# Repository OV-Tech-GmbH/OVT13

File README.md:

# OVT13
Open-source thin-and-light 13" laptop
## Table of contents

1. Electronics
   - Keyboard PCB
   - Webcam PCB
   - Trackpad PCBs
2. Mechanical
   - Keyboard
3. Software
   - Keyboard firmware and source files

## Details of content

1. Electronics
   - Keyboard PCB: <br /> <br /> 
***General description:*** <br /> <br /> This module is a separate standalone and thinly-designed electromechanical keyboard for the open-source laptop. It provides a distinct hardware abstraction via USB2.0 connectivity to simplify integration into a laptop or computer system. An RP2040 microcontroller constantly evaluates the states of the keyswitches and controls the lightning. Regarding the power supply only a voltage of 5V DC is needed to completly supply the electronics, all other voltages for digital logic and LED-driving are being generated on the PCB. Once connected to an USB Host in a computer system, the microcontroller acts as an USB Device and registers itself as an USB HID keyboard device. With this configuration no custom drivers are needed which contributes to an os-independend (Windows, Linux, etc.) and timeless integration concept. The firmware of the microcontroller is based on the open-source keyboard framework QMK. Once an USB-connection is established, standard scancodes are being transmitted to the computer system which then will be mapped into keycodes. The hardware connectivity to the mainboard of the laptop is realized over an spring-header connector receptable which includes all electrical signals and the power supply. For the firmware to load onto the RP2040, only one pin of the spring header receptable must change its logical state. The RP2040 register itself as an USB-memory device which then can be accessed via the os` filesystem. It is possible to load the firmware file per drag&drop onto the microcontroller. <br /> <br /> 
***Electrical specification***<br /> <br /> 
__PCB front view__

The PCB-front consists of the keyswitches from the manufacturer Khail. The design integrates a complete set of keys without the numerical part. Keycaps can be assembled on top of the keyswitches.
Inside the keyswitches there is a transparent cabin to integrate LED components and other small components like the anti-ghosting diode. Per keyswitch a white LED and an RGB LED is placed to keep the option to build a keyboard with either white backlightning or RGB backlightning. 
<br /><br /> __PCB back view__ <br />
On the backside of the PCB there are all remaining components located. The remaing components include the microcontroller RP2040 and its peripheral circuitry, voltage generation, ESD-protection and other parts of the keyswitch matrix.
 <br />
<br /> __PCB layerstack and routing__ <br /> The Layerstack consists four layers of copper and it is taken from the 4-Layer JLCPCB stackup JLC04161H-7628. An impedance profile 90Ohms is included for the USB connection. The layerstack looks as follows: Top-layer: Signal, Mid1-layer: GND, Mid2-layer PWR/GND, Bottom-layer: Signal 
On the top layer all signals and power supplies regarding the LED-backlightning are routed:

The Mid1-layer includes a continuous ground plane to provide good electrical characteristics. The Mid2-layer is a mix of power plane distribution and ground islands, especially for the dense placement of the microcontroller and surrounding circuitry:

On the bottom layer consist of the routing of the keyswitch matrix, the microcontroller and the remaining circuitry.

   - Trackpad PCBs:<br /> <br /> 
***General description:***<br /> <br /> The design of the trackpad module consists of two printed circuit boards. The first one consists of the touch-sensitive matrix which, can be influenced by the user. In order to keep variations and negative impact factors away from the matrix, the touch sensing IC and its digital communication partner are located on an evaluation board. Both boards are connected via an flex-pcb cable section so the touch IC can to read the sensing matrix.<br /> <br /> 
<br /> <br />
__1. Trackpad sensor PCB electrical specification:__<br /> <br />
The top side of the PCB consists of touch-sensitive elements in the form of diamonds arranged in rows and columns. The gaps between the diamonds form capacitive elements that can be controlled and thus read by the touch IC. The capacitive elements generate an electric field, that is deflected when the user`s finger approaches. The change in the field and thus the resulting capacitance and charge can be measured and converted into a finger position sensor. <br /> <br />

<br /> <br />
On the backside of the pcb a flex pcb connector and a snap dome are located. The flex connector is used to connect the board to another board on which a touch IC is located via a flex cable. The snap dome is being used to generate the function of a button press. When pressed, the entire row and colum is shorted and the rapid change in capacitance and therefore charge is recognised and interpreted as a button press. <br /> <br />

<br /> <br />__2. Trackpad evaluation PCB electrical specification:__<br /> <br />
This PCB is designed as a flex PCB with two stiffened sections. The section where all the components are located is fitted with a FR4-stiffener. The section designed as a flex cable contains no stiffeners in order to utilise the flexibility of a flex cable. The last section is the connector tongue itself and the stiffener is made out of polyimide to fulfil the thickness insertion requierements of the ffc-connector on the trackpad PCB.
<br /> <br />
<br /> <br />
The evaluation board is used to collect trackpad touch data and turn it into an USB HID mouse. This level of integration abstracts the custom interface to a simple USB connection without the need for special drivers or hardware to utilise the touch data. The IQS9150 IC performs the sampling and processing of the trackpad touches and snapdome clicks and reports the data to an RP2040, which performs some further processing, such as interpreting a click event as a left or right mouse button click. The RP2040 streams the touch data in USB HID mouse format to an USB host and thus acts as an I2C USB bridge. Additional connections for programming and evaluating the two ICs and other devices such as test buttons are provided on the board for development purposes. The final board will contain only the two ICs, some necessary external circuitry and an USB connection. This makes integration into the laptop easy and follows the concept of a timeless and modular design.
<br /> <br />
<br /> <br />

3. Mechanical
   - Keyboard: -

4. Software
   - Keyboard PCB: The firmware of the keyboard was created using the framework QMK. The framework provides all basic keyboard functions such as matrix scanning, USB communication, lightning and much more. Therefore, only one module of the keyboard project has been created for the specific design of the keyboard. Minor modifications were made to the QMK core to compile the firmware for the RP2040 microcontroller. A standard English keyboard layout (QWERTY) was used. Details of the code project can be found in the subfolder for the keyboard software.

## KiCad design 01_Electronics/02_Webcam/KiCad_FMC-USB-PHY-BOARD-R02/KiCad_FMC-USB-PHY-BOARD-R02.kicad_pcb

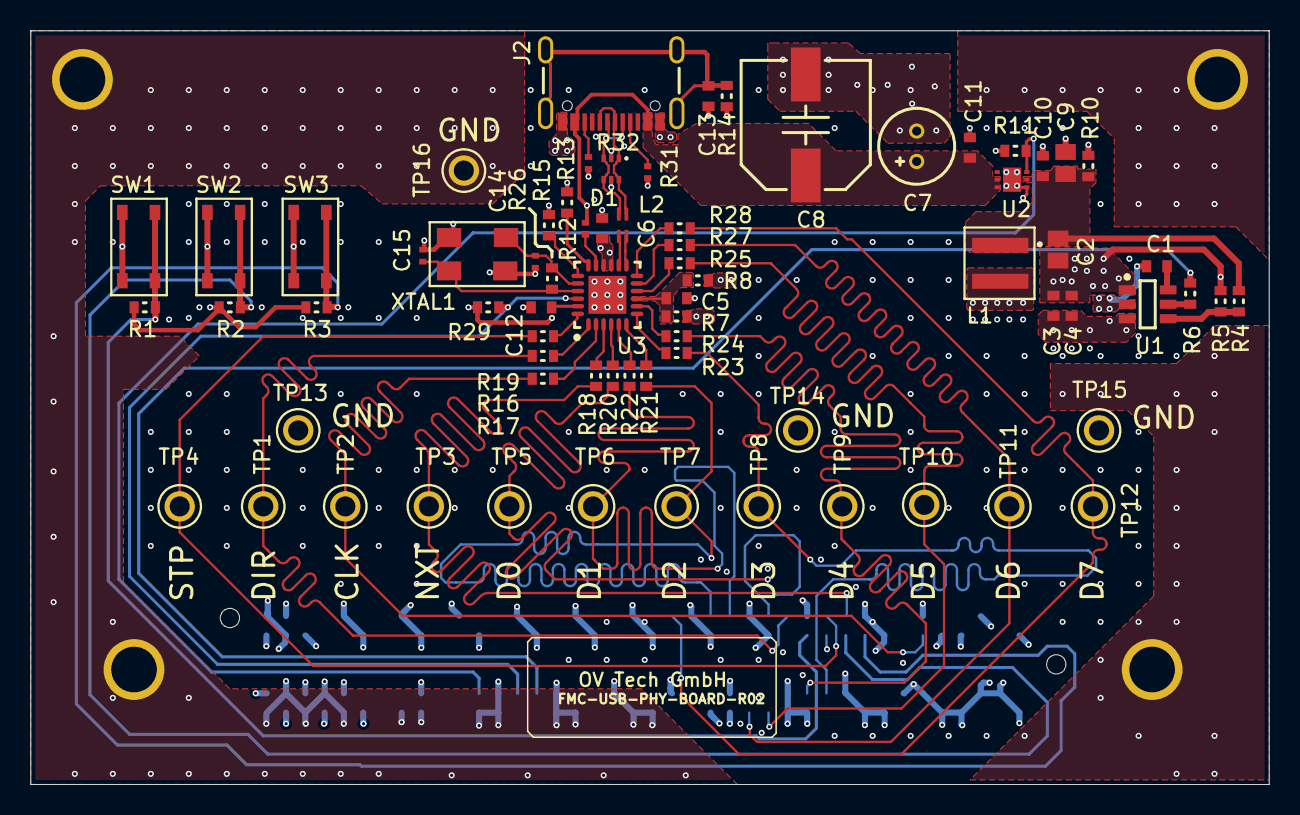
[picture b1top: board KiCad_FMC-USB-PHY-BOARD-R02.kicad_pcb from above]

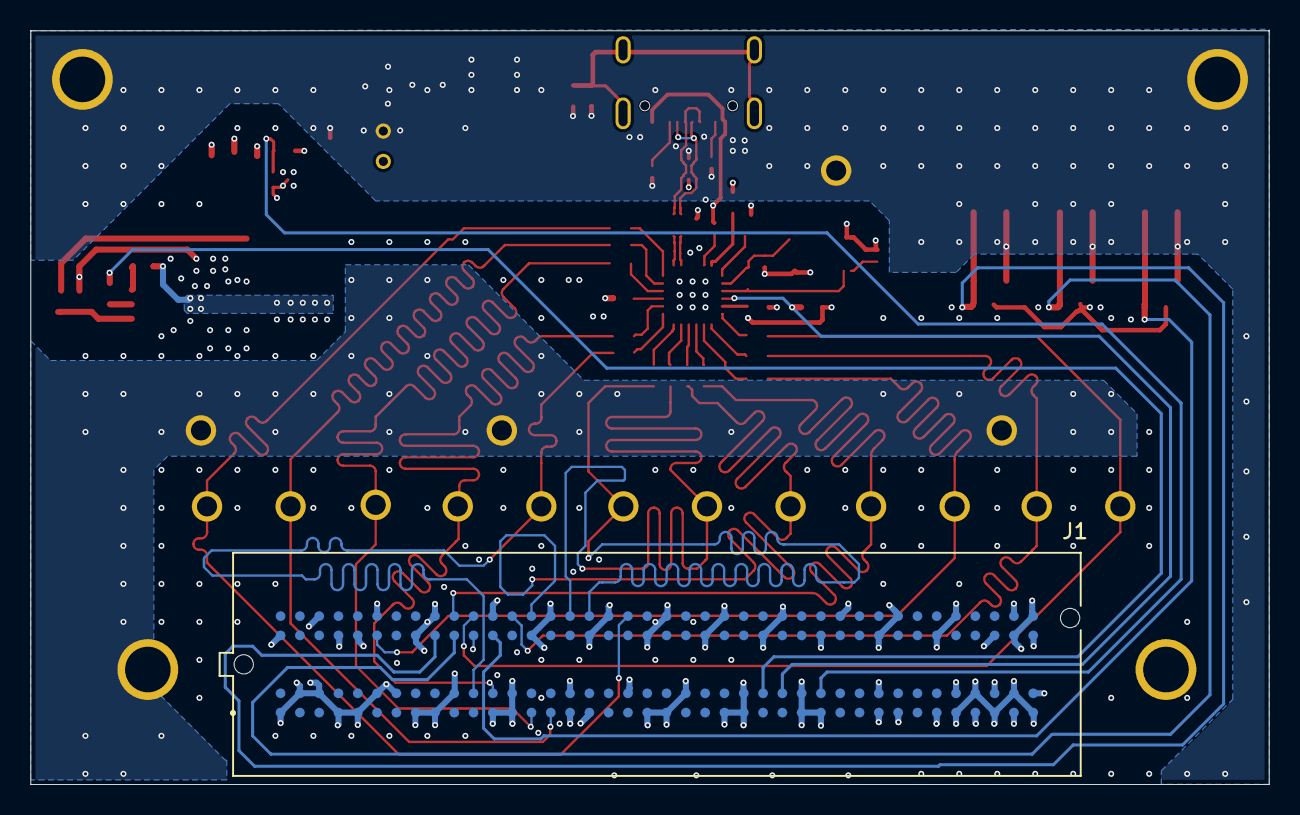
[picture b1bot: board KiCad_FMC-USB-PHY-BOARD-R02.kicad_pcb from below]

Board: 4 copper layers, 81.5 x 49.6 mm, 77 parts (3 on the bottom side), 54 nets.

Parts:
C1, C4, C5, C10, C11, C13: 100nF 100V; CAPC1608X10L
C2: 33µF 10V; CAPC2012X14L
C3: 2.2µF 35V; CAPC1608X10L
C6, C12: 1µF 16V; CAPC1608X10L
C7: 100µF 10V; CAP_Radial_5x8mm
C8: 22µF 63V; CAPAE9083X70N
C9: 10µF 16V; CAPC2012X14L
C14, C15: 30pF 50V; CAPC1005X06L
D1: 82400152; WE-TVS_SOT563
J1: ASP-134604-01; BOARD-TO-BOARD CON SAMTEC_ASP-134604-01
J2: TYPE-C 16PIN 2MD(073); USB Type C - TYPE-C 16PIN 2MD(073)
L1: 6.8µH 3.75A; WE-MAPI_4030
L2: 90Ohm 100mA; WE-CNSW_0603
MP1, MP2, MP3, MP4: MP_MOUNT_3MM_Plated; MP_3MM_PLATED
R1, R2, R3, R11, R29: 22kOhm 1%; RESC1608X04L
R4: 100kOhm 1%; RESC1608X04L
R5: 13.7kOhm 1%; RESC1608X04L
R6, R7, R8, R13, R16, R18, R19, R20, R21, R22, R23, R24, R25, R27, R28: 0 Ohm; RESC1608X04L
R10: 10kOhm 1%; RESC1608X04L
R12: 10k 1%; RESC1005X04L
R14: 330Ohm 1%; RESC1608X04L
R15: 8.06kOhm 1%; RESC1608X04L
R17: 33Ohm 1%; RESC1608X04L
R26: 1MOhm 1%; RESC1608X04L
R31, R32: 5.1k 1%; RESC1005X04L
SW1, SW2, SW3: PTS815 SJM 250 SMTR LFS; SW_TACT_PTS815 SJM 250 SMTR LFS
TP1, TP2, TP3, TP4, TP5, TP6, TP7, TP8, TP9, TP10, TP11, TP12, TP13, TP14, TP15, TP16: 4952; TP_KEYSTONE_4952
U1: TPS54308DDC; SOT95P280X110-6N
U2: AP21510FM-7; QFN50P201X181X60_HS-7N
U3: USB3343; QFN50P400X400X100_HS-25M
XTAL1: ECS-260-18-30B-AGM-TR; XTAL_ECX-53B_5X3.2X0.85

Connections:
1V8_ADJ: J1.G39, J1.H40, R1.2, R2.2, R3.2, R7.2, R29.2
3V3: C6.1, J1.C39, J1.D32, J1.D36, J1.D38, J1.D40, R8.2, R13.2, U3.15, U3.16
5V0: C2.1, C9.1, C10.1, L1.1, R4.1, R10.2, U2.2
12V0: C3.1, C4.1, J1.C35, J1.C37, U1.3
DEBUG_SW1: J1.G12, R1.1, SW1.3, SW1.4
DEBUG_SW2: J1.G10, R2.1, SW2.3, SW2.4
DEBUG_SW3: J1.G9, R3.1, SW3.3, SW3.4
GND: C2.2, C3.2, C4.2, C5.2, C6.2, C7.2, C8.2, C9.2, C10.2, C11.2, C12.2, C13.2, C14.2, C15.2, D1.2, J1.C1, J1.C4, J1.C5, J1.C8, J1.C9, J1.C12, J1.C13, J1.C16, J1.C17, J1.C20, J1.C21, J1.C24, J1.C25, J1.C28, J1.C29, J1.C32, J1.C33, J1.C36, J1.C38, J1.C40, J1.D2, J1.D3, J1.D6, J1.D7, J1.D10, J1.D13, J1.D16, J1.D19, J1.D22, J1.D25, J1.D28, J1.D37, J1.D39, J1.G1, J1.G4, J1.G5, J1.G8, J1.G11, J1.G14, J1.G17, J1.G20, J1.G23, J1.G26, J1.G29, J1.G32, J1.G35, J1.G38, J1.G40, J1.H3, J1.H6, J1.H9, J1.H12, J1.H15, J1.H18, J1.H21, J1.H24, J1.H27, J1.H30, J1.H33, J1.H36, J1.H39, J2.A1/B12, J2.A12/B1, MP1.1, MP2.1, MP3.1, MP4.1, R5.1, R10.1, R11.1, R14.1, R15.2, R31.1, R32.1, SW1.1, SW1.2, SW2.1, SW2.2, SW3.1, SW3.2, TP13.TP, TP14.TP, TP15.TP, TP16.TP, U1.1, U2.1, U2.7, U3.25, XTAL1.2, XTAL1.4
NetC1_1: C1.1, U1.6
NetC1_2: C1.2, L1.2, U1.2
NetC5_1: C5.1, R7.1, R8.1, U3.9
NetC12_1: C12.1, U3.23
NetC13_1: C13.1, J2.SHD, R14.2
NetJ2_A5: J2.A5, R31.2
NetJ2_B5: J2.B5, R32.2
NetR4_2: R4.2, R5.2, U1.4
NetR6_2: R6.2, U1.5
NetR12_1: R12.1, U3.17
NetR13_1: R13.1, U3.18
NetR16_2: R16.2, U3.1
NetR17_2: R17.2, U3.2
NetR18_2: R18.2, U3.3
NetR19_2: R19.2, U3.24
NetR20_2: R20.2, U3.4
NetR21_2: R21.2, U3.5
NetR22_2: R22.2, U3.6
NetR23_2: R23.2, U3.7
NetR24_2: R24.2, U3.8
NetR25_2: R25.2, U3.10
NetR27_2: R27.2, U3.11
NetR28_2: R28.2, U3.12
USB_ESD_N: D1.3, D1.4, J2.A7, J2.B7, L2.2
USB_ESD_P: D1.1, D1.6, J2.A6, J2.B6, L2.3
USB_N: L2.1, U3.14
USB_P: L2.4, U3.13
USB_PHY_RST: J1.D27, R29.1, U3.22
USB_RBIAS: R15.1, U3.19
USB_ULPI_CLK: J1.G6, R17.1, TP2.TP
USB_ULPI_D0: J1.H14, R20.1, TP5.TP
USB_ULPI_D1: J1.H16, R21.1, TP6.TP
USB_ULPI_D2: J1.H17, R22.1, TP7.TP
USB_ULPI_D3: J1.D11, R23.1, TP8.TP
USB_ULPI_D4: J1.D12, R24.1, TP9.TP
USB_ULPI_D5: J1.C14, R25.1, TP10.TP
USB_ULPI_D6: J1.C15, R27.1, TP11.TP
USB_ULPI_D7: J1.H19, R28.1, TP12.TP
USB_ULPI_DIR: J1.H13, R16.1, TP1.TP
USB_ULPI_NXT: J1.H10, R18.1, TP3.TP
USB_ULPI_STP: J1.H11, R19.1, TP4.TP
USB_VBUS_DISABLE: J1.D26, R6.1
USB_XTAL_IN: C15.1, R26.2, U3.21, XTAL1.3
USB_XTAL_OUT: C14.1, R26.1, U3.20, XTAL1.1
VBUS: C7.1, C8.1, C11.1, D1.5, J2.A4/B9, J2.A9/B4, R12.2, U2.5, U2.6
VBUS_EN: J1.D29, R11.2, U2.3

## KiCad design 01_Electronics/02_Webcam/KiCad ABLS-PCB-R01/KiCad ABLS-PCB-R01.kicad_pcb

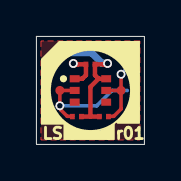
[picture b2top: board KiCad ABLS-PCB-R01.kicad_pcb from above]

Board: 2 copper layers, 6.0 x 6.0 mm, 9 parts (1 on the bottom side), 4 nets.

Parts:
C1: 470nF 10V; CAPC0603X03L
R1, R2: 2.1k 1%; RESC0603X03L
TP1, TP2, TP3, TP4: Testpoint 0.5mm; TP_0.50mm
U1: VEML3235; Light Sensor_VEML3235
U2: Ambient Light Sensor Module; ABLS-R01-sensor-Module Footprint

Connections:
GND: C1.2, TP2.TP, U1.1, U2.2, U2.3, U2.4
SCL: R2.1, TP4.TP, U1.5, U2.6
SDA: R1.1, TP3.TP, U1.2, U2.5
VCCA3.3: C1.1, R1.2, R2.2, TP1.TP, U1.6, U2.1

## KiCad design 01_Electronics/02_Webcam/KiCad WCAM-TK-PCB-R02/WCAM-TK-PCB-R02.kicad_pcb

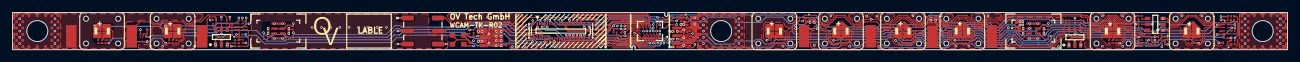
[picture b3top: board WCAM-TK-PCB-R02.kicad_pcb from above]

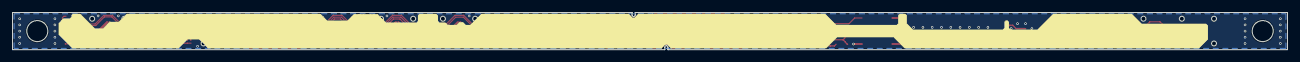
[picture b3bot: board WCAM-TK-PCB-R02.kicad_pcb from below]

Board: 6 copper layers, 206.0 x 6.0 mm, 179 parts (26 on the bottom side), 113 nets.

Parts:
C1, C2, C5, C6: 1µF 25V; CAPC1005X06L
C3, C4: 10µF 10V; CAPC1005X06L
C7, C10, C11, C12, C15, C16, C17, C20, C21, C22, C23, C26, C27, C35: 470nF 10V; CAPC0603X03L
C8, C9, C13, C14, C18, C19: OPT; CAPC0603X03L
C24, C25, C28, C29, C30, C31, C32, C33, C34: 1uF 6.3V; CAPC0603X03L
J1: 5055504020; BOARD-TO-BOARD 40POL_505550-4020
J2, J3, J4, J5, J6, J7, J8, J9: Custom Light Pipe Diffusor; LIGHT_PIPE_DIFFUSOR_CUSTOM
J10, J11, J14, J15, J18, J19, J22: 3-2199250-3; Contact Pad_3.2mm_3-2199250-3
J12, J16, J20: 74AUP1G14GM,115; PSON50P140X100X50-6L
J13, J17, J21: 74AUP1G74GT,115; PSON50P100X50-8L
LED1, LED2, LED3, LED4, LED5, LED6, LED7, LED8: LTRBR37G-4R4S-0125-0; LED 120X120 LTRB R37G RGB
Q1, Q2, Q3, Q4, Q7: SSM3K15ACT,L3F; DFN65P100X50-3L
Q5, Q6: SSM3J56ACT,L3F; DFN65P100X50-3L
R1, R4, R5, R8, R11, R13, R18, R20, R23, R25, R30, R32, R35, R37, R42, R44, R50, R58: 240R 1%; RESC0603X03L
R2, R12, R24, R36: 150R 1%; RESC0603X03L
R3, R14, R26, R38, R51, R52, R53: 1.5k 1%; RESC0603X03L
R6, R17, R29, R41, R49, R55, R59: 18k 1%; RESC0603X03L
R7, R15, R16, R19, R27, R28, R31, R39, R40, R43: 1k 1%; RESC0603X03L
R9, R10, R21, R22, R33, R34, R45, R46, R47, R48, R54, R56, R57, R62: 0R 1%; RESC0603X03L
R60: 10k 1%; RESC0603X03L
R61: OPT; RESC0603X03L
R63: 33R 1%; RESC0603X03L
TP1, TP2, TP3, TP4, TP5, TP6, TP7, TP8, TP9, TP10, TP11, TP12, TP13, TP14, TP15, TP16, TP17, TP18, TP19, TP20, TP21, TP22, TP23, TP24, TP25, TP26, TP27, TP28, TP29, TP30, TP31: Testpoint 0.5mm; TP_0.50mm
U1, U2: TLV74033PDQNR; X2SON-DFN
U3, U4, U5: TTP232-CA6; SOT95P285X126-6L
U6, U7: SPK0641HT4H-1; MIC_SPK0641HT4H-1
U8: Ambient Light Sensor Module R01; ABLS-R01-AMBIENT LIGHT SENSOR MODULE
U9: TLV74018PDQNR; X2SON-DFN
U10: OV02740-H34A-Z; BGA34C53P7X5_386X292X388
U11: TLV74012PDQNR; X2SON-DFN
U12: TLV74028PDQNR; X2SON-DFN
U13: ECS-2520MV-240-BN-TR; Oscillator_ECS-2520MV

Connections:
AGND: C28.2, R62.1, U10.B7, U10.C1
AVDD: C28.1, R57.2, TP30.TP, U9.3, U10.A1, U10.C4, U10.C7, U10.E1
BAT_FCH_LED: J1.7, LED1.1
BAT_LOW_LED: J1.9, LED2.1
CAMERA_DISABLE: J17.3, LED6.1
CAMERA_ENABLE: J1.6, J17.5, LED5.1, R58.1, TP16.TP
CAM_EN: J16.2, TP13.TP, U4.3
CAM_~DIS: J17.6, TP12.TP, U4.1
CAM_~EN: J16.4, J17.1
CAP_CAM_DIS: R21.1, U4.6
CAP_CAM_DIS_PAD: C13.1, J15.1, R21.2
CAP_CAM_EN: R22.1, U4.4
CAP_CAM_EN_PAD: C14.1, J14.1, R22.2
CAP_MIC_DIS: R34.1, U5.4
CAP_MIC_DIS_PAD: C19.1, J19.1, R34.2
CAP_MIC_EN: R33.1, U5.6
CAP_MIC_EN_PAD: C18.1, J18.1, R33.2
CAP_WIFI_DIS: R9.1, U3.6
CAP_WIFI_DIS_PAD: C8.1, J11.1, R9.2
CAP_WIFI_EN: R10.1, U3.4
CAP_WIFI_EN_PAD: C9.1, J10.1, R10.2
CM_D: J17.2, R28.1
CM_~SD: J17.7, R27.1
CSI_CLK_N: J1.37, U10.D5
CSI_CLK_P: J1.35, U10.E5
CSI_D0_N: J1.31, U10.D4
CSI_D0_P: J1.29, U10.E4
CSI_D1_N: J1.23, U10.D6
CSI_D1_P: J1.25, U10.E6
DOVDD: C26.1, C35.1, R51.2, R52.2, R53.2, R54.2, TP27.TP, U10.A3, U10.C6, U11.3, U13.1, U13.4
DVDD: C27.1, R56.2, TP28.TP, U10.A7, U10.D3, U10.E7
GLOBAL_PWM: J1.10, R4.2, R13.2, R25.2, R37.2
GND: C1.2, C2.2, C3.2, C4.2, C5.2, C6.2, C7.2, C8.2, C9.2, C10.2, C11.2, C12.2, C13.2, C14.2, C15.2, C16.2, C17.2, C18.2, C19.2, C20.2, C21.2, C22.2, C23.2, C24.2, C25.2, C26.2, C27.2, C29.2, C30.2, C31.2, C32.2, C33.2, C34.2, C35.2, J1.5, J1.21, J1.26, J1.27, J1.30, J1.32, J1.33, J1.36, J1.38, J1.39, J1.MT, J12.3, J13.4, J16.3, J17.4, J20.3, J21.4, J22.1, Q1.2, Q2.2, Q3.2, Q4.2, Q7.2, R6.1, R17.1, R29.1, R41.1, R59.2, R62.2, TP8.TP, TP31.TP, U1.2, U1.5, U2.2, U2.5, U3.2, U4.2, U5.2, U6.5, U6.6, U6.7, U6.8, U7.3, U7.5, U7.6, U7.7, U7.8, U8.2, U8.3, U8.4, U9.2, U9.5, U10.B1, U10.C2, U10.C5, U10.D7, U10.E3, U11.2, U11.5, U12.2, U12.5, U13.2
LSNS_SCL: J1.4, U8.6
LSNS_SDA: J1.2, U8.5
MIC_D: J21.2, R40.1
MIC_DISABLE: J21.3, LED8.1, R50.1
MIC_EN: J20.2, TP17.TP, U5.1
MIC_~DIS: J21.6, TP18.TP, U5.3
MIC_~EN: J20.4, J21.1
MIC_~SD: J21.7, R39.1
MLED_EN: J21.5, LED7.1, TP21.TP
NetC24_1: C24.1, R54.1, U9.1
NetC25_1: C25.1, C30.1, C34.1, Q6.3, TP26.TP, U9.4, U11.4, U12.3, U12.4
NetC29_1: C29.1, R56.1, U11.1
NetC31_1: C31.1, R57.1, U12.1
NetJ1_1: J1.1, R47.2, R48.1, TP22.TP
NetJ1_3: J1.3, R45.2, R46.1, TP23.TP
NetLED1_2: LED1.2, R3.1
NetLED1_3: LED1.3, R1.1
NetLED1_4: LED1.4, R2.1
NetLED2_2: LED2.2, R8.1
NetLED2_3: LED2.3, R5.1
NetLED2_4: LED2.4, R7.1
NetLED3_2: LED3.2, R14.1
NetLED3_3: LED3.3, R11.1
NetLED3_4: LED3.4, R12.1
NetLED4_2: LED4.2, R20.1
NetLED4_3: LED4.3, R18.1
NetLED4_4: LED4.4, R19.1
NetLED5_2: LED5.2, R26.1
NetLED5_3: LED5.3, R23.1
NetLED5_4: LED5.4, R24.1
NetLED6_2: LED6.2, R32.1
NetLED6_3: LED6.3, R30.1
NetLED6_4: LED6.4, R31.1
NetLED7_2: LED7.2, R38.1
NetLED7_3: LED7.3, R35.1
NetLED7_4: LED7.4, R36.1
NetLED8_2: LED8.2, R44.1
NetLED8_3: LED8.3, R42.1
NetLED8_4: LED8.4, R43.1
NetQ1_1: Q1.1, R4.1, R6.2
NetQ1_3: Q1.3, R1.2, R2.2, R3.2, R5.2, R7.2, R8.2, TP4.TP
NetQ2_1: Q2.1, R13.1, R17.2, TP9.TP
NetQ2_3: Q2.3, R11.2, R12.2, R14.2, R18.2, R19.2, R20.2, TP10.TP
NetQ3_1: Q3.1, R25.1, R29.2, TP14.TP
NetQ3_3: Q3.3, R23.2, R24.2, R26.2, R30.2, R31.2, R32.2, TP15.TP
NetQ4_1: Q4.1, R37.1, R41.2, TP19.TP
NetQ4_3: Q4.3, R35.2, R36.2, R38.2, R42.2, R43.2, R44.2, TP20.TP
NetQ5_1: Q5.1, R49.1, R50.2, TP25.TP
NetQ6_1: Q6.1, Q7.3, R55.2, TP29.TP
NetQ7_1: Q7.1, R58.2, R59.1
NetR45_1: R45.1, U6.1
NetR46_2: R46.2, U7.1
NetR47_1: R47.1, U6.2
NetR48_2: R48.2, U7.2
NetR60_1: R60.1, U10.A4
NetR63_1: R63.1, U13.3
SNS_FSIN: J1.14, U10.B3
SNS_GPIO: J1.22, U10.A5
SNS_PWDNB: J1.12, U10.B2
SNS_SCL: J1.24, U10.B6
SNS_SDA: J1.20, U10.B5
SNS_SID: R53.1, U10.A6
SNS_STROBE: J1.18, R60.2
SNS_VH: C33.1, U10.D1
SNS_VN: C32.1, U10.D2
SNS_XSHDN: J1.11, R51.1, U10.C3
SNS_XSHDN2: R52.1, U10.A2
SNS_XVCLK: R61.1, R63.2, U10.B4
VCC3.3: C5.1, C10.1, C11.1, C15.1, C16.1, C20.1, C21.1, J12.6, J13.8, J16.6, J17.8, J20.6, J21.8, R15.2, R16.2, R27.2, R28.2, R39.2, R40.2, TP3.TP, U2.1
VCC5.0: C2.1, C3.1, C4.1, C6.1, J1.28, J1.34, J1.40, Q6.2, R55.1, TP2.TP, U1.3, U1.4, U2.3, U2.4
VCCA3.3: C1.1, C7.1, C12.1, C17.1, Q5.2, R49.2, TP1.TP, TP5.TP, U1.1, U3.5, U4.5, U5.5, U8.1
VCC_MIC: C22.1, C23.1, Q5.3, TP24.TP, U6.3, U6.4, U7.4
WIFI_EN: J12.2, TP7.TP, U3.3
WIFI_~DIS: J13.6, TP6.TP, U3.1
WIFI_~EN: J12.4, J13.1
WI_D: J13.2, R16.1
WI_~SD: J13.7, R15.1
WLED_DIS: J13.3, LED4.1
WiFi_ENABLE: J1.8, J13.5, LED3.1, TP11.TP
XVCLK: J1.16, R61.2

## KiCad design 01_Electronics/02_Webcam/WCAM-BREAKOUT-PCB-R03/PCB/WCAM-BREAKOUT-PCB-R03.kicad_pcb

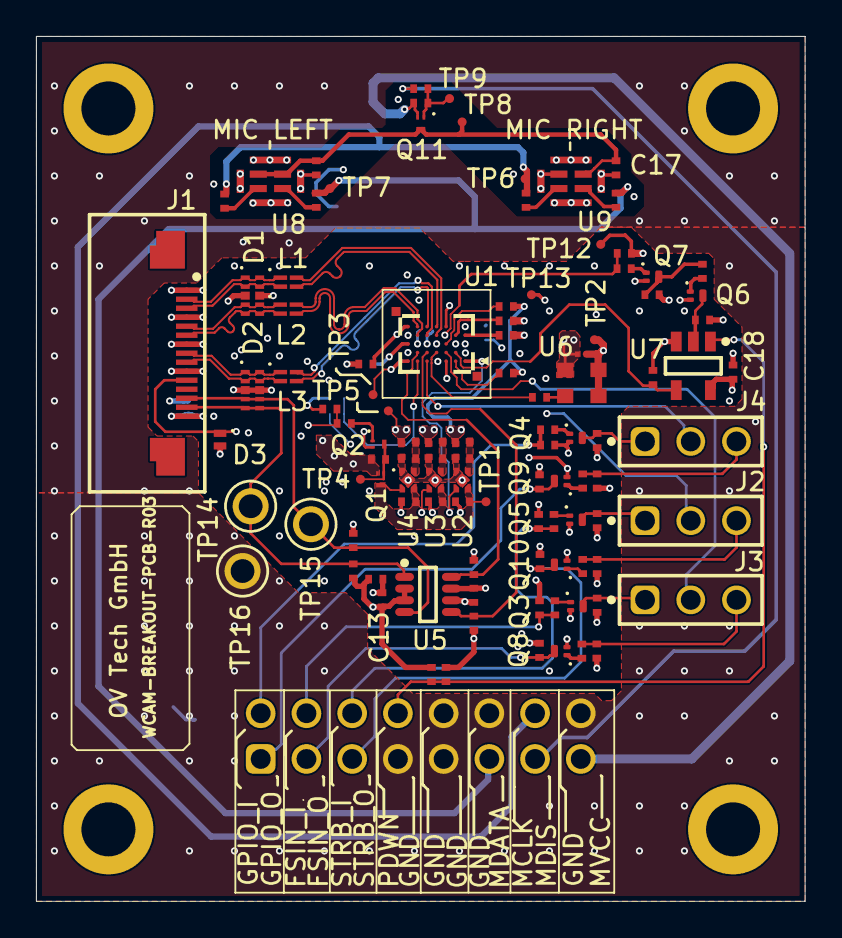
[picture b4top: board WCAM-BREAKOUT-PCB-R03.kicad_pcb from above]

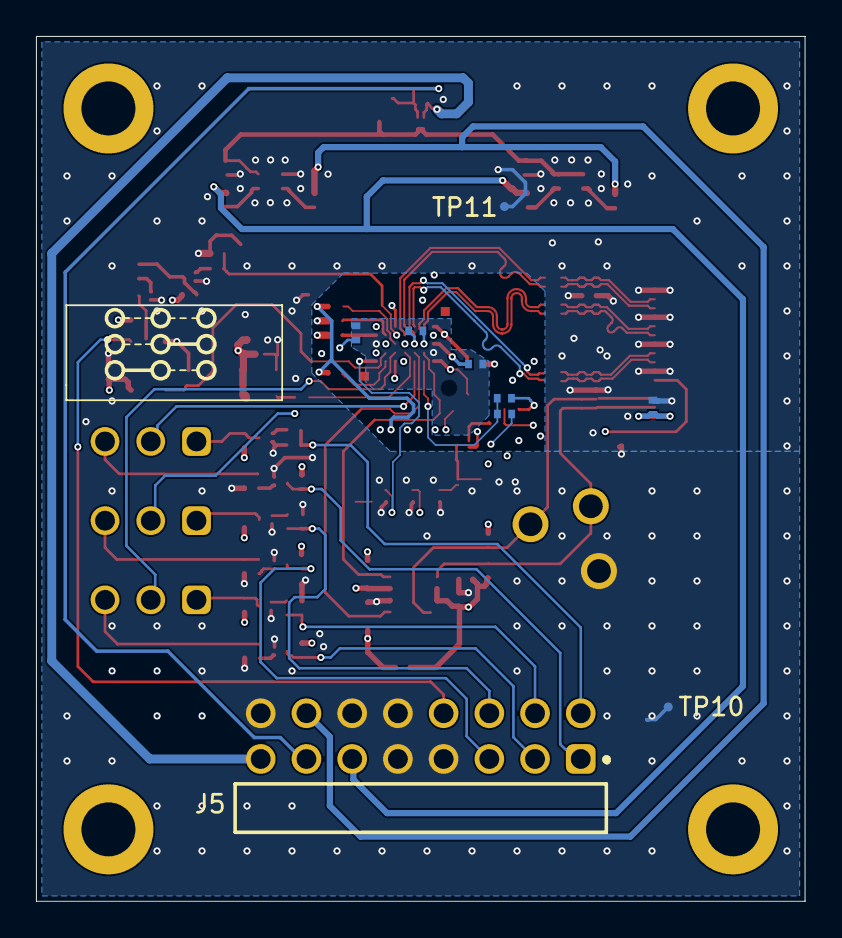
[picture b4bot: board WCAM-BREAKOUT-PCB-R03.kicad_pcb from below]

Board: 4 copper layers, 42.7 x 48.1 mm, 114 parts (9 on the bottom side), 73 nets.

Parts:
C1, C2, C3, C6, C7, C8, C9, C10, C11, C12: 1µF 25V; CAPC1005X06L
C4, C5, C16, C17: 470nF 25V; CAPC1005X06L
C13, C14, C18: 100nF 16V; CAPC1005X06L
C15: 470nF 10V; CAPC0603X03L
D1, D2: ESD7504MUTAG; QFN50P250X100X55-10L
D3: PESD5V5C1UL; DFN65P100X50-2N
J1: F32Q-1A7H1-11015; FFC 15pol 0.5mm F32Q-1A7H1-11015
J2, J3, J4: 61300311121; BOARD TO BOARD Pinheader WE_61300311121
J5: 61301621021; BOARD TO BOARD Pinheader WE_61301621021
L1, L2, L3: 90Ohm 100mA; CAF-50P85X64-4N
Q1, Q11: SSM3J56ACT,L3F; DFN65P100X50-3L
Q2: SSM3K15ACT,L3F; DFN65P100X50-3L
Q3, Q4, Q5, Q6, Q7, Q8, Q9, Q10: PMZ130UNEYL; DFN65P98X50-3N
R1, R2, R4, R9, R44, R45: 0Ohm 1%; RESC1005X04L
R3, R6: 15k 1%; RESC1005X04L
R5, R47: 240R 1%; RESC1005X04L
R7, R8, R16, R17, R18, R48, R49: 1.5k 1%; RESC1005X04L
R10, R11, R12, R13: 3.3k 1%; RESC1005X04L
R14: 27R 1%; RESC1005X04L
R15, R24, R25, R26, R29, R30, R31, R39, R40, R41: 10k 1%; RESC1005X04L
R19, R22, R28, R33, R34, R35: 22k 1%; RESC1005X04L
R20, R21, R23, R27, R32, R36, R37, R38: 100R 1%; RESC1005X04L
R42, R43: 33 1%; RESC1005X04L
R46: 18k 1%; RESC1005X04L
TP1, TP2, TP3, TP4, TP5, TP6, TP7, TP8, TP9, TP10, TP11, TP12, TP13: Testpoint 0.5mm; TP_0.50mm
TP14, TP15, TP16: 4952; TP_Keystone_4952
U1: OV02740-H34A-Z; BGA34C53P7X5_386X292X388
U2: TLV74018PDQNR; X2SON-DFN
U3: TLV74012PDQNR; X2SON-DFN
U4: TLV74028PDQNR; X2SON-DFN
U5: TCA9416DDFR; TSOP65P280X110-8N
U6: ECS-2520MV-240-BN-TR; Oscillator_ECS-2520MV
U7: 74LVC1G08GV; SOT95P275X110-5N
U8, U9: SPK0641HT4H-1; MIC_SPK0641HT4H-1

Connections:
AGND: C3.2, R9.2, U1.B7, U1.C1
AVDD: C3.1, R4.1, TP5.TP, U1.A1, U1.C4, U1.C7, U1.E1, U2.3
CAM_I2C_SCL: D2.4, D2.7, J1.13, R11.1, TP15.TP, U5.4
CAM_I2C_SDA: D2.5, D2.6, J1.14, R10.1, TP14.TP, U5.1
CAM_nRST: D3.1, J1.11, R5.1, R6.1
CON_CSI_CLK_N: D2.1, D2.10, J1.8, L3.1
CON_CSI_CLK_P: D2.2, D2.9, J1.9, L3.4
CON_CSI_D0_N: D1.1, D1.10, J1.2, L1.1
CON_CSI_D0_P: D1.2, D1.9, J1.3, L1.4
CON_CSI_D1_N: D1.4, D1.7, J1.5, L2.1
CON_CSI_D1_P: D1.5, D1.6, J1.6, L2.4
CSI_CLK_N: L3.2, U1.D5
CSI_CLK_P: L3.3, U1.E5
CSI_D0_N: L1.2, U1.D4
CSI_D0_P: L1.3, U1.E4
CSI_D1_N: L2.2, U1.D6
CSI_D1_P: L2.3, U1.E6
DOVDD: C5.1, C14.1, C15.1, C18.1, R1.1, R7.1, R12.2, R13.2, R16.2, R17.2, R18.2, R19.2, R22.2, R34.2, R48.1, R49.1, TP2.TP, U1.A3, U1.C6, U3.3, U5.7, U6.1, U6.4, U7.5
DVDD: C4.1, R2.1, R32.2, R33.2, TP3.TP, U1.A7, U1.D3, U1.E7
FSIN_3V3_INPUT: J5.4, R20.2, R24.2
FSIN_3V3_OUTPUT: J5.3, Q8.3, R29.1
GND: C1.2, C2.2, C4.2, C5.2, C6.2, C7.2, C8.2, C9.2, C10.2, C11.2, C12.2, C13.2, C14.2, C15.2, C16.2, C17.2, C18.2, D1.3, D1.8, D2.3, D2.8, D3.2, J1.1, J1.4, J1.7, J1.10, J5.7, J5.9, J5.10, J5.12, J5.16, Q2.2, Q3.2, Q4.2, Q5.2, Q6.2, Q7.2, Q8.2, Q9.2, Q10.2, R6.2, R8.1, R9.1, R15.1, R24.1, R25.1, R26.1, R28.1, R33.1, R39.1, R40.1, R41.1, TP10.TP, TP11.TP, TP12.TP, TP13.TP, TP16.TP, U1.B1, U1.C2, U1.C5, U1.D7, U1.E3, U2.2, U2.5, U3.2, U3.5, U4.2, U4.5, U5.6, U6.2, U7.3, U8.5, U8.6, U8.7, U8.8, U9.3, U9.5, U9.6, U9.7, U9.8
GPIO_3V3_INPUT: J5.2, R21.2, R25.2
GPIO_3V3_OUTPUT: J5.1, Q9.3, R30.1
MIC_CLK: J5.14, R44.2, R45.1, TP6.TP
MIC_DATA: J5.11, R42.2, R43.1, TP7.TP
MIC_DISABLE: J5.13, R47.1
NetC1_1: C1.1, C7.1, C11.1, Q1.3, TP1.TP, U2.4, U3.4, U4.3, U4.4
NetC2_1: C2.1, R1.2, U2.1
NetC8_1: C8.1, R2.2, U3.1
NetC12_1: C12.1, R4.2, U4.1
NetJ2_1: J2.1, Q5.3, R18.1
NetJ2_3: J2.3, R38.1, R41.2
NetJ3_1: J3.1, Q3.3, R16.1
NetJ3_3: J3.3, R36.1, R39.2
NetJ4_1: J4.1, Q4.3, R17.1
NetJ4_3: J4.3, R37.1, R40.2
NetQ1_1: Q1.1, Q2.3, R3.2, TP4.TP
NetQ2_1: Q2.1, R5.2
NetQ3_1: Q3.1, R20.1
NetQ4_1: Q4.1, R21.1
NetQ5_1: Q5.1, R23.1
NetQ6_1: Q6.1, R27.1
NetQ7_1: Q7.1, R32.1
NetQ7_3: Q7.3, R22.1, R27.2
NetQ8_1: Q8.1, R36.2
NetQ9_1: Q9.1, R37.2
NetQ10_1: Q10.1, R38.2
NetQ11_1: Q11.1, R46.1, R47.2, TP9.TP
NetR14_2: R14.2, U6.3
NetR42_1: R42.1, U8.1
NetR43_2: R43.2, U9.1
NetR44_1: R44.1, U8.2
NetR45_2: R45.2, U9.2
NetR48_2: R48.2, U1.C3
NetR49_2: R49.2, U1.A2
PWDNB_EXT: J5.8, R34.1, R35.1, U7.1
PWDNB_POWER_SUPPLY: Q6.3, R19.1, U7.2
SCL_1V8: R12.1, U1.B6, U5.8
SDA_1V8: R13.1, U1.B5, U5.5
SNS_FSIN: J3.2, U1.B3
SNS_GPIO: J4.2, U1.A5
SNS_PWDNB: R28.2, U1.B2, U7.4
SNS_SID: R7.2, R8.2, U1.A6
SNS_STROBE: J2.2, U1.A4
SNS_VH: C9.1, U1.D1
SNS_VN: C10.1, U1.D2
SNS_XVCLK: R14.1, U1.B4
STROBE_3V3_INPUT: J5.6, R23.2, R26.2
STROBE_3V3_OUTPUT: J5.5, Q10.3, R31.1
VCC3.3: C6.1, C13.1, J1.15, Q1.2, R3.1, R10.2, R11.2, R15.2, R29.2, R30.2, R31.2, R35.2, U5.2, U5.3
VCC3.3MIC: J5.15, Q11.2, R46.2
VCC_MIC: C16.1, C17.1, Q11.3, TP8.TP, U8.3, U8.4, U9.4

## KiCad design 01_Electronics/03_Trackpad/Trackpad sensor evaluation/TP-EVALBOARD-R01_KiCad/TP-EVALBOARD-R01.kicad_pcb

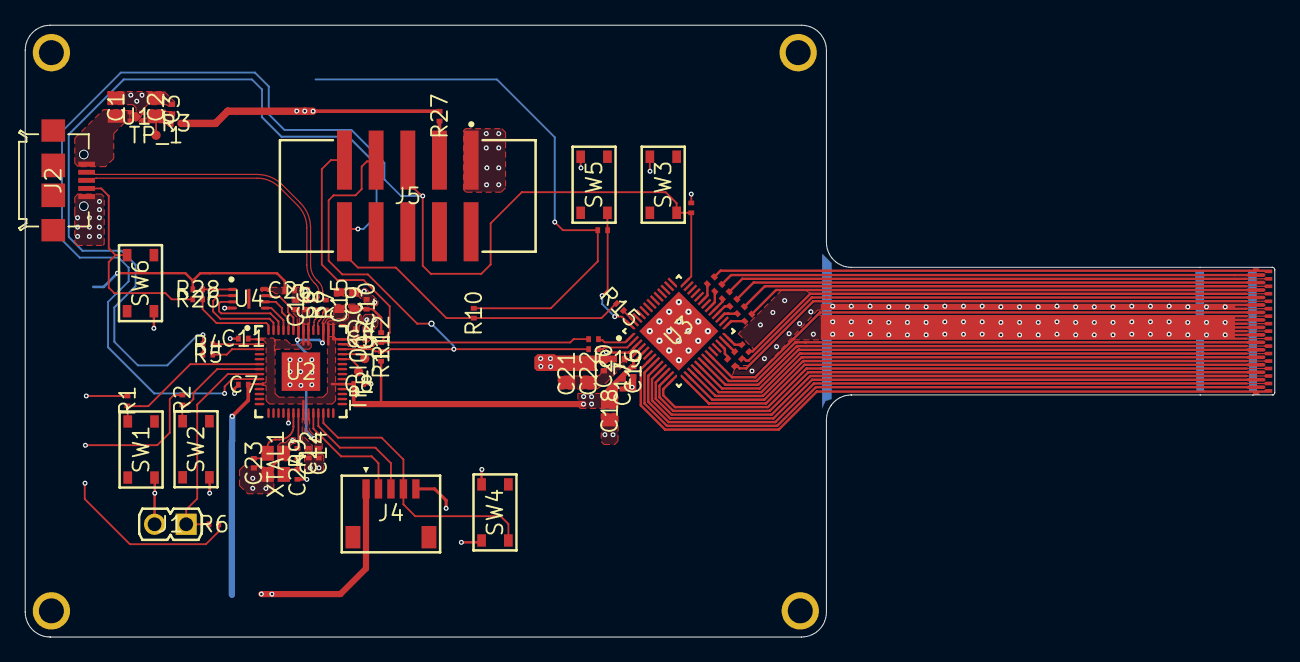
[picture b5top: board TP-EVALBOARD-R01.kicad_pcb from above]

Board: 2 copper layers, 100.3 x 49.1 mm, 77 parts (0 on the bottom side), 72 nets.

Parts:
C1, C2, C18, C21, C22: CAPC2012X14L
C3, C4, C5, C6, C7, C8, C10, C11, C12, C13, C14, C16, C17, C19, C20, C23, C24, C25, C26: CAPC1005X06L
C9, C15: CAPC1608X10L
J1: Pin Header 2Pol 61300211121
J2: USB-TYPE MICRO B_629105136821
J3: WIRE-TO-BOARD_RECEPTABLE_FH35C-33S-0.3SHW(50)
J4: Wire-to-Board SM05B-SRSS-TB
J5: WIRE-TO-BOARD_WE_61231020621
MP1, MP2, MP3, MP4: MP_2MM
R1, R2, R3, R4, R5, R6, R7, R8, R9, R10, R11, R12, R13, R14, R15, R16, R17, R18, R19, R20, R21, R22, R23, R24, R25, R26, R27, R28: RESC1005X04L
SW1, SW2, SW3, SW4, SW5, SW6: SW_TACT_PTS815 SJM 250 SMTR LFS
TP_1: TP_0.75mm
TP_IO1, TP_IO2: TP_0.75mm
U1: X2SON-DFN
U2: QFN40P700X700X90_HS-57L
U3: QFN40P600X600X80_HS-53M
U4: QFN50P300X200X60_HS-9L
XTAL1: XTAL_ECX-2236B2_250X200X60

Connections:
3V3: C4.1, C5.1, C6.1, C7.1, C8.1, C9.1, C10.1, C11.1, C12.1, C16.1, C17.1, C18.1, C26.1, J4.1, R1.1, R2.1, R3.2, R6.2, R10.2, R11.2, R12.2, R24.2, R27.1, R28.1, U2.1, U2.10, U2.22, U2.33, U2.42, U2.43, U2.44, U2.48, U2.49, U3.5, U4.8
3V3_REG: C2.1, C3.1, R3.1, TP_1.TP, U1.1
/USB_BOOT_IN: J2.4, R26.1, SW6.1
GND: C1.2, C2.2, C3.2, C4.2, C5.2, C6.2, C7.2, C8.2, C9.2, C10.2, C11.2, C12.2, C13.2, C14.2, C15.2, C16.2, C17.2, C18.2, C19.2, C20.2, C21.2, C22.2, C23.2, C24.2, C25.2, C26.2, J1.2, J2.5, J3.15, J3.16, J3.17, J3.18, J3.19, J3.20, J3.21, J3.23, J3.24, J4.5, J5.1, SW1.4, SW2.4, SW3.4, SW4.3, SW4.4, SW5.4, SW6.4, U1.2, U1.5, U2.19, U2.57, U3.3, U3.53, U4.4, XTAL1.2, XTAL1.4
GPIO4_RND: R1.2, SW1.1, U2.6
GPIO5_RND: R2.2, SW2.1, U2.7
GPIO6_SNAP_DOME: J1.1, R6.1, U2.8
GPIO7_IQS_nRST: C25.1, J5.5, SW3.1, U2.9, U3.39
I2C_SCL: J5.9, R12.1, R14.1, U2.41
I2C_SDA: J5.7, R11.1, R13.1, U2.40
IQS_RDY: J5.10, R4.2, R5.2, R10.1, R15.1
IQS_RX0: J3.25, R16.2
IQS_RX1: J3.33, R25.2
IQS_RX2: J3.31, R22.2
IQS_RX3: J3.29, R20.2
IQS_RX4: J3.27, R18.2
IQS_RX5: J3.26, R17.2
IQS_RX6: J3.28, R19.2
IQS_RX7: J3.32, R23.2
IQS_RX8: J3.30, R21.2
IQS_SW_IN: R24.1, SW5.1, U3.52
IQS_TX0: J3.14, U3.20
IQS_TX1: J3.12, U3.18
IQS_TX2: J3.2, U3.8
IQS_TX3: J3.4, U3.10
IQS_TX4: J3.6, U3.12
IQS_TX5: J3.8, U3.14
IQS_TX6: J3.10, U3.16
IQS_TX7: J3.22, U3.21
IQS_TX8: J3.1, U3.7
IQS_TX9: J3.3, U3.9
IQS_TX10: J3.5, U3.11
IQS_TX11: J3.7, U3.13
IQS_TX12: J3.9, U3.15
IQS_TX13: J3.11, U3.17
IQS_TX14: J3.13, U3.19
NetC24_1: C24.1, R9.1, XTAL1.3
NetJ5_3: J5.3, R27.2
NetR4_1: R4.1, U2.2
NetR5_1: R5.1, U2.3
NetR13_2: R13.2, U3.2
NetR14_2: R14.2, U3.1
NetR15_2: R15.2, U3.51
NetR16_1: R16.1, U3.24
NetR17_1: R17.1, U3.25
NetR18_1: R18.1, U3.26
NetR19_1: R19.1, U3.27
NetR20_1: R20.1, U3.29
NetR21_1: R21.1, U3.30
NetR22_1: R22.1, U3.31
NetR23_1: R23.1, U3.32
NetR25_1: R25.1, U3.34
NetTP_IO1_TP: TP_IO1.TP, U2.38
NetTP_IO2_TP: TP_IO2.TP, U2.39
QSPI_SCLK: U2.52, U4.6
QSPI_SD0: U2.53, U4.5
QSPI_SD1: U2.55, U4.2
QSPI_SD2: U2.54, U4.3
QSPI_SD3: U2.51, U4.7
QSPI_SS: R26.2, R28.2, U2.56, U4.1
RUN: J4.4, SW4.1, U2.26
SWCLK: J4.2, U2.24
SWDIO: J4.3, U2.25
USB_D_N: J2.2, R7.1
USB_D_P: J2.3, R8.1
USB_MCU_D_N: R7.2, U2.46
USB_MCU_D_P: R8.2, U2.47
VBUS: C1.1, J2.1, U1.3, U1.4
VREG: C19.1, C20.1, C21.1, C22.1, U3.4
VREG_VOUT: C13.1, C14.1, C15.1, U2.23, U2.45, U2.50
XIN: C23.1, U2.20, XTAL1.1
XOUT: R9.2, U2.21

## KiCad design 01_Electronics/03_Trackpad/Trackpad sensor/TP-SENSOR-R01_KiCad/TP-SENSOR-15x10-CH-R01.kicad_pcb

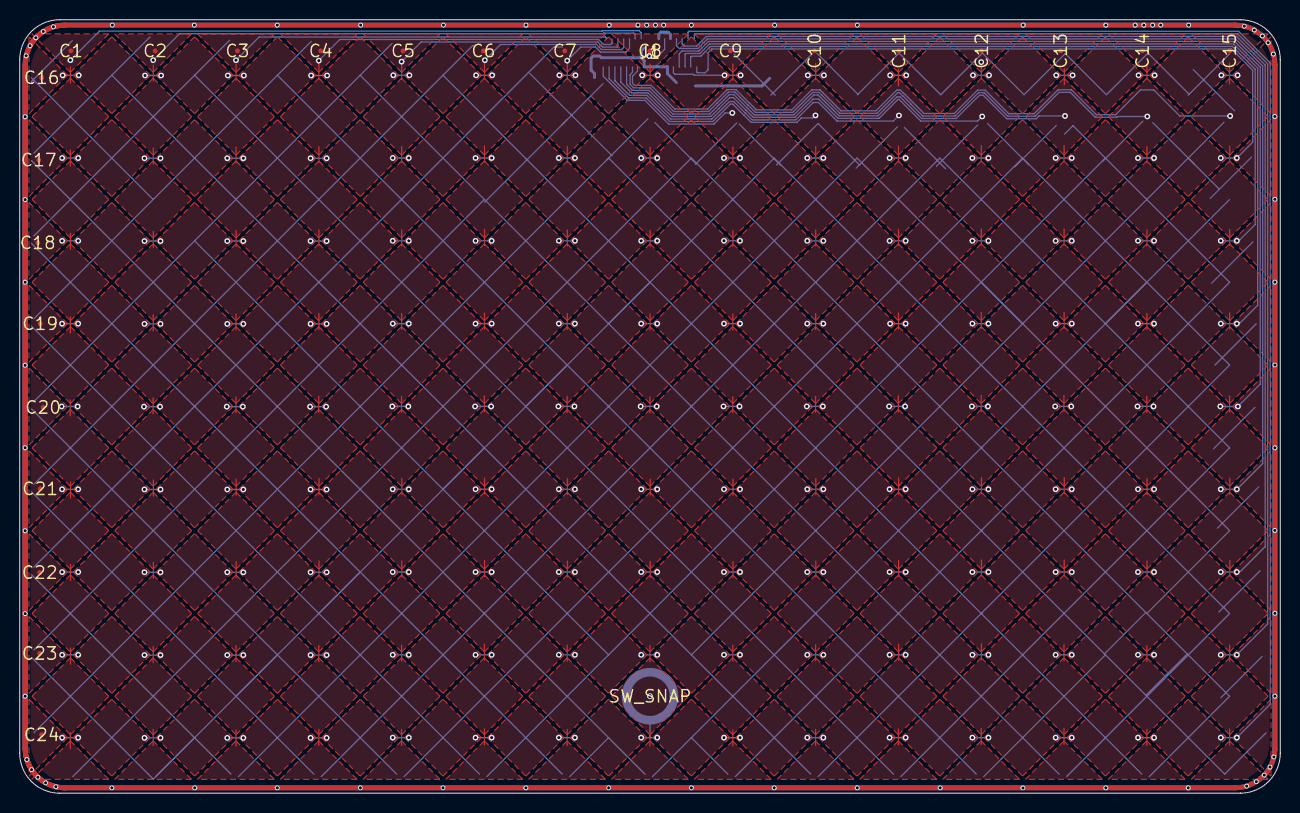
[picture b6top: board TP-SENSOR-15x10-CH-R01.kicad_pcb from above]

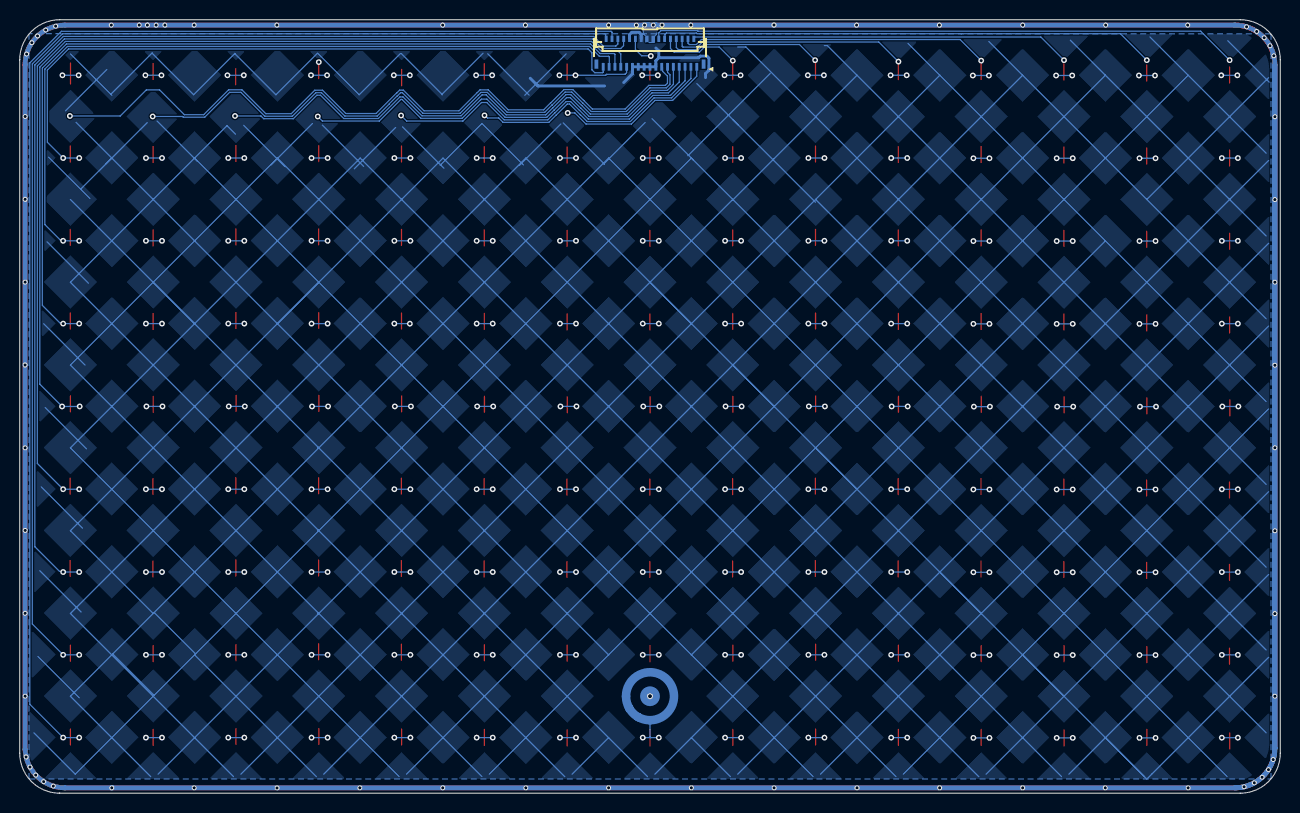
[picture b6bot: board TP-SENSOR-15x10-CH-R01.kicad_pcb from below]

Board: 2 copper layers, 129.4 x 79.4 mm, 26 parts (2 on the bottom side), 26 nets.

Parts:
C1, C2, C3, C4, C5, C6, C7, C8, C9, C10, C11, C12, C13, C14, C15: CAP_TRACKPAD_TX_CLM
C16, C17, C18, C19, C20, C21, C22, C23, C24: CAP_TRACKPAD_RX_ROW
J1: FFC 33pol 0.3mm FH35C-33S-0.3SHW
SW_SNAP: SNAPDOME_RCG05200N

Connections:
EMI-GND: J1.16, J1.18
GND: J1.15, J1.17, J1.19, J1.20, J1.21, J1.23, J1.24
TP-SENS-RX0: C16.RX_ROW, J1.25
TP-SENS-RX1: C17.RX_ROW, J1.33
TP-SENS-RX2: C18.RX_ROW, J1.31
TP-SENS-RX3: C19.RX_ROW, J1.29
TP-SENS-RX4: C20.RX_ROW, J1.27
TP-SENS-RX5: C21.RX_ROW, J1.26
TP-SENS-RX6: C22.RX_ROW, J1.28
TP-SENS-RX7: C23.RX_ROW, J1.32
TP-SENS-RX8: C24.RX_ROW, J1.30, SW_SNAP.1
TP-SENS-TX0: C1.TX_CLM, J1.14
TP-SENS-TX1: C2.TX_CLM, J1.12
TP-SENS-TX2: C3.TX_CLM, J1.2
TP-SENS-TX3: C4.TX_CLM, J1.4
TP-SENS-TX4: C5.TX_CLM, J1.6
TP-SENS-TX5: C6.TX_CLM, J1.8
TP-SENS-TX6: C7.TX_CLM, J1.10
TP-SENS-TX7: C8.TX_CLM, J1.22, SW_SNAP.2
TP-SENS-TX8: C9.TX_CLM, J1.1
TP-SENS-TX9: C10.TX_CLM, J1.3
TP-SENS-TX10: C11.TX_CLM, J1.5
TP-SENS-TX11: C12.TX_CLM, J1.7
TP-SENS-TX12: C13.TX_CLM, J1.9
TP-SENS-TX13: C14.TX_CLM, J1.11
TP-SENS-TX14: C15.TX_CLM, J1.13

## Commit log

2024-03-02 Initial commit keyboard and webcam PCB
2024-03-24 Added Keyboard and Webcam electronics in KiCAD format
2024-03-25 Adding webcam sensor breakout board and keyboard mechanics
2024-03-25 Create LICENSE
2024-03-26 Add keyboard firmware sources
2024-04-22 Update README.md
    Added table of contents and details of content (keyboard)
2024-04-23 Update README.md
    Added the description of the KB-PCB Rev2
2024-05-05 Update README.md
    Added keyboard software description.
2024-07-17 Upload for Trackpad data
    This commit contains all data for the trackpad sensor and evaluation board.
2024-07-17 Update README.md
    Work in progress trackpad
2024-07-24 Update README.md
    Completed readme for trackpad description
2026-06-02 Added breakout boards for developing
    Added altium designer and KiCad projects:
    * FMC-USB-PHY-BOARD-R02
    * WCAM-BREAKOUT-PCB-R03
    * KiCad_WCAM-BREAKOUT-PCB-R03
    * KiCad_FMC-USB-PHY-BOARD-R02

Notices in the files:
01_Electronics/02_Webcam/KiCad_FMC-USB-PHY-BOARD-R02/KiCad_FMC-USB-PHY-BOARD-R02.kicad_pcb:
This hardware design is licensed under the CERN Open Hardware Licence Version 2 - Strongly Reciprocal (CERN-OHL-S-2.0).
